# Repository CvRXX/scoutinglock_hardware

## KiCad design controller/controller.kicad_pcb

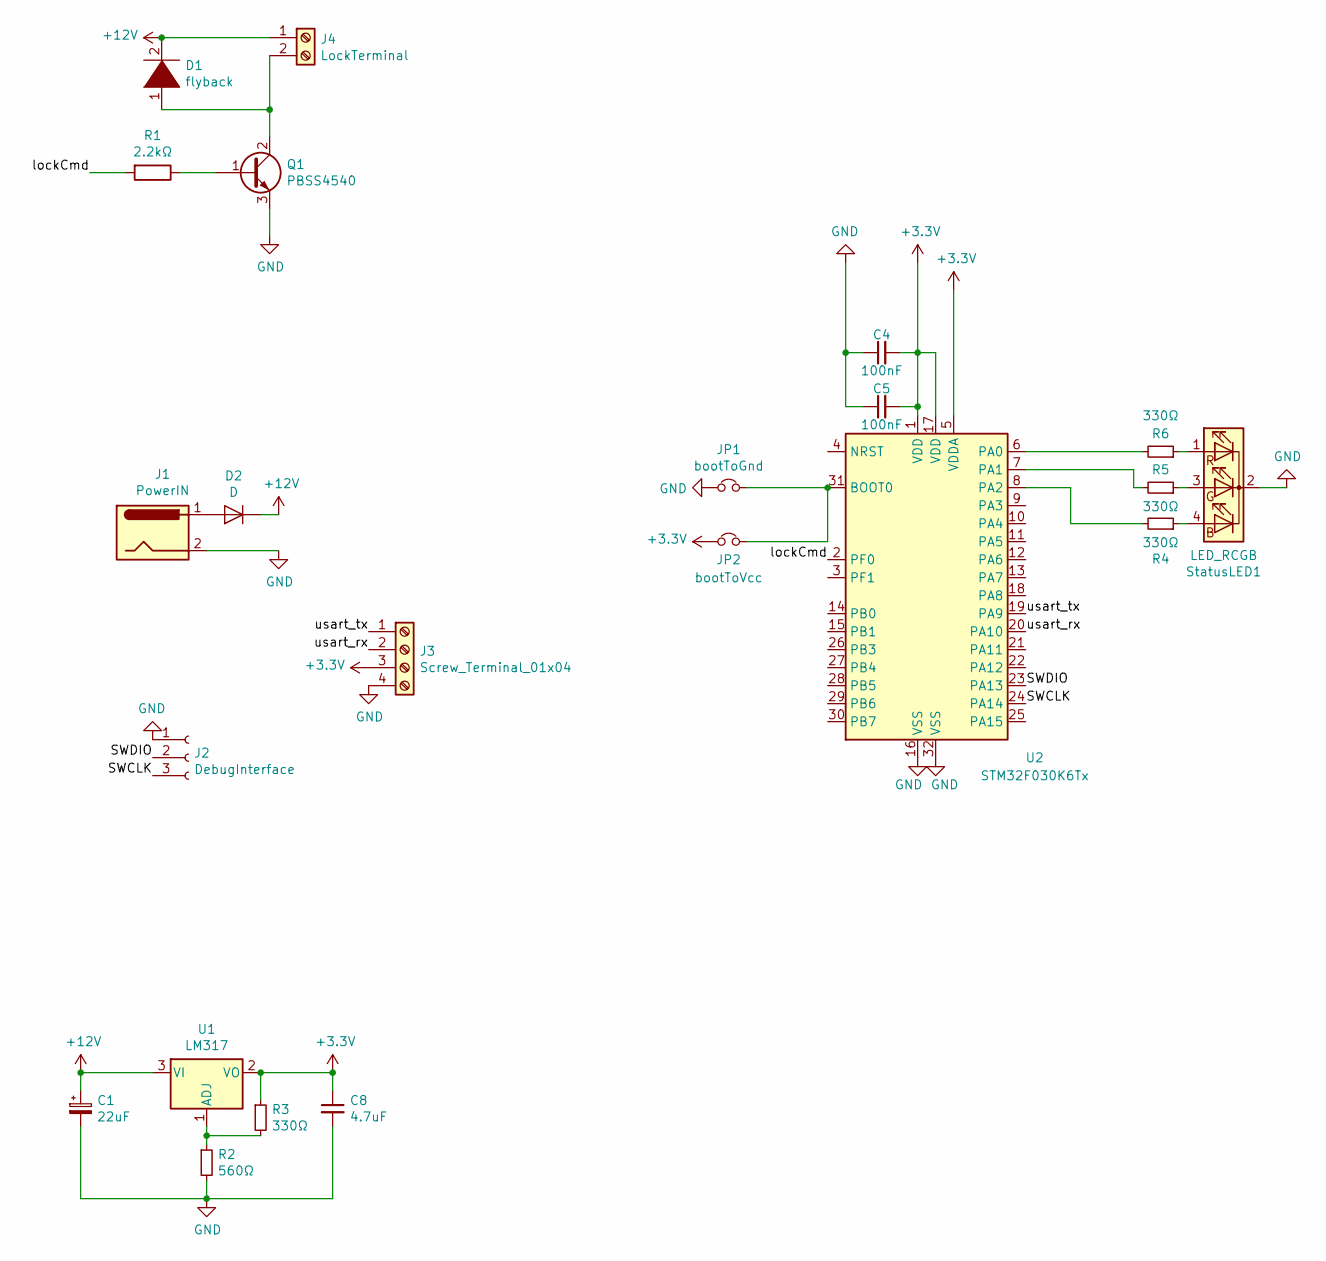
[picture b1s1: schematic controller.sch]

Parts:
C1: 22uF; CP_Radial_D5.0mm_P2.00mm
C4, C5: 100nF; C_0603_1608Metric_Pad1.05x0.95mm_HandSolder
C8: 4.7uF; C_0603_1608Metric_Pad1.05x0.95mm_HandSolder
D1: flyback; D_DO-201AD_P12.70mm_Horizontal
D2: D; D_DO-201AD_P12.70mm_Horizontal
J1: PowerIN; BarrelJack_CUI_PJ-063AH_Horizontal_CircularHoles
J2: DebugInterface; SolderWirePad_1x03_P7.62mm_Drill2.5mm
J3: Screw_Terminal_01x04; TerminalBlock_bornier-4_P5.08mm
J4: LockTerminal; TerminalBlock_bornier-2_P5.08mm
JP1: bootToGnd; SolderJumper-2_P1.3mm_Open_Pad1.0x1.5mm
JP2: bootToVcc; SolderJumper-2_P1.3mm_Open_Pad1.0x1.5mm
Q1: PBSS4540; SOT-223
R1: 2.2kΩ; R_0805_2012Metric_Pad1.15x1.40mm_HandSolder
R2: 560Ω; R_0603_1608Metric_Pad1.05x0.95mm_HandSolder
R3, R4, R5, R6: 330Ω; R_0603_1608Metric_Pad1.05x0.95mm_HandSolder
StatusLED1: LED_RCGB; LED_D5.0mm-4_RGB
U1: LM317; TO-220-3_Vertical
U2: STM32F030K6Tx; LQFP-32_7x7mm_P0.8mm

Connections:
+3V3: C4.2, C5.2, C8.1, J3.3, JP2.1, R3.1, U1.2 (VO), U2.1 (VDD), U2.5 (VDDA), U2.17 (VDD)
+12V: C1.1, D1.2 (A), D2.1 (K), J4.1, U1.3 (VI)
/SWCLK: J2.3, U2.24 (PA14)
/SWDIO: J2.2, U2.23 (PA13)
/lockCmd: R1.2, U2.2 (PF0)
/usart_rx: J3.2, U2.20 (PA10)
/usart_tx: J3.1, U2.19 (PA9)
GND: C1.2, C4.1, C5.1, C8.2, J1.2, J2.1, J3.4, JP1.1, Q1.3 (E), R2.2, StatusLED1.2 (K), U2.16 (VSS), U2.32 (VSS)
unnamed: D1.1 (K), J4.2, Q1.2 (C)
unnamed: D2.2 (A), J1.1
unnamed: JP1.2, JP2.2, U2.31 (BOOT0)
unnamed: Q1.1 (B), R1.1
unnamed: R2.1, R3.2, U1.1 (ADJ)
unnamed: R4.1, StatusLED1.4 (BA)
unnamed: R4.2, U2.8 (PA2)
unnamed: R5.1, StatusLED1.3 (GA)
unnamed: R5.2, U2.7 (PA1)
unnamed: R6.1, StatusLED1.1 (RA)
unnamed: R6.2, U2.6 (PA0)

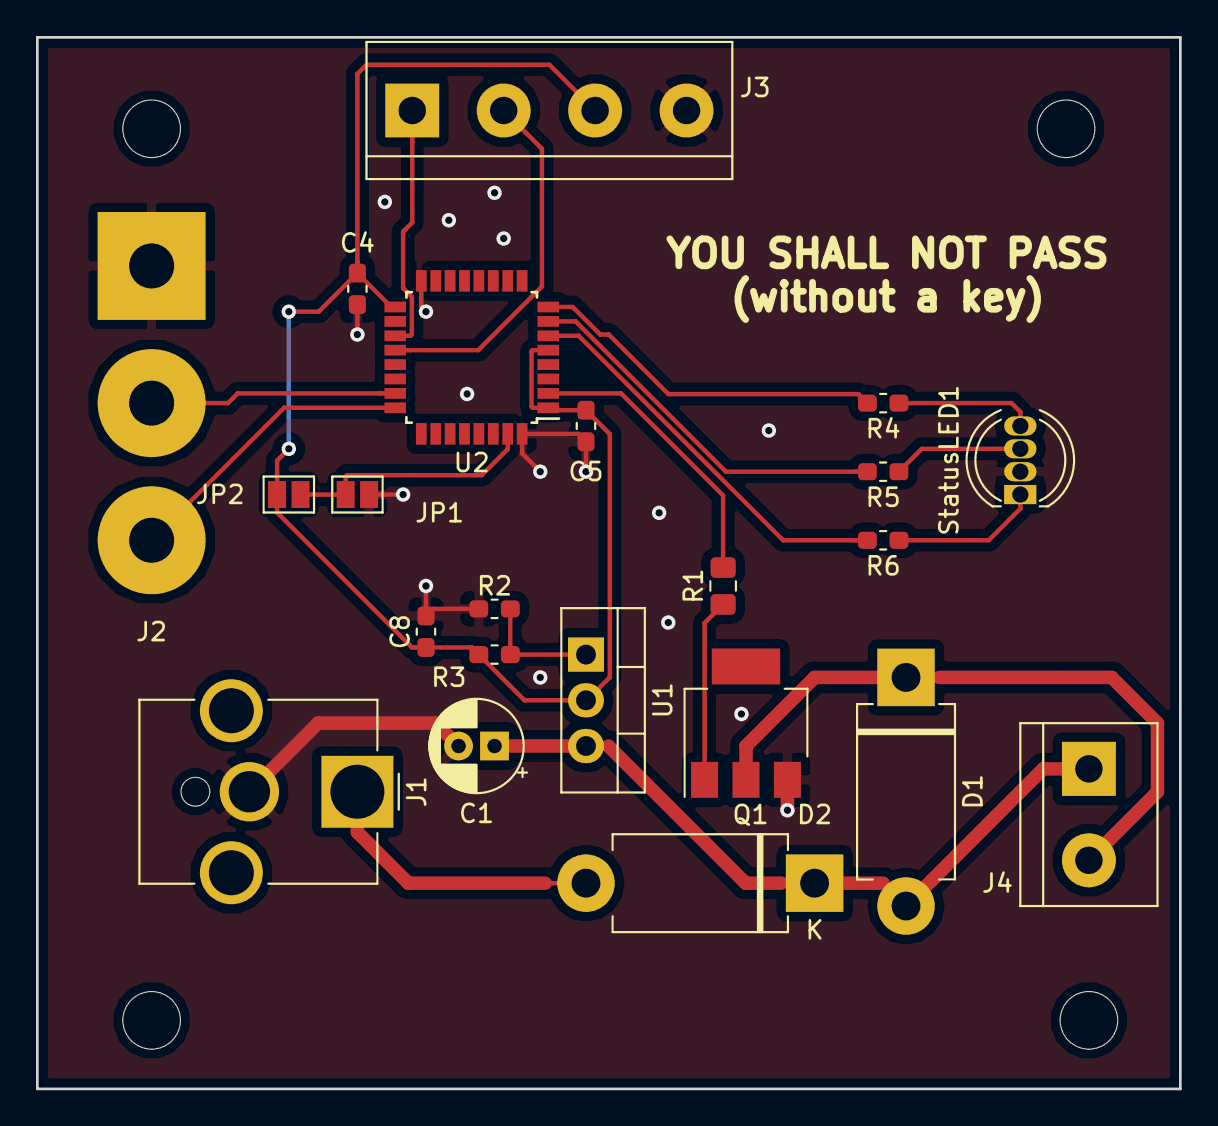
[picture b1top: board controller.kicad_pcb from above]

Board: 2 copper layers, 63.5 x 58.4 mm, 22 parts (0 on the bottom side), 19 nets.

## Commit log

2018-11-04 adding v1.0
2018-11-21 adding current sensing
2018-12-03 stated working on the case for the nfc reader
